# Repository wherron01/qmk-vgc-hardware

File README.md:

# QMK Video Game Controller Hardware
### The OSH HID PC video game controller powered by QMK
KiCAD Files for the PCB.

Implemented using 
- [SparkFun Thumb Joysticks](https://www.sparkfun.com/products/9032)
- [C&K PTS645 Switches](https://www.ckswitches.com/products/switches/product-details/Tactile/PTS645/)
- [Teensy LC](https://www.pjrc.com/teensy/teensyLC.html)

### [OSHPark Project](https://oshpark.com/shared_projects/MazId014)

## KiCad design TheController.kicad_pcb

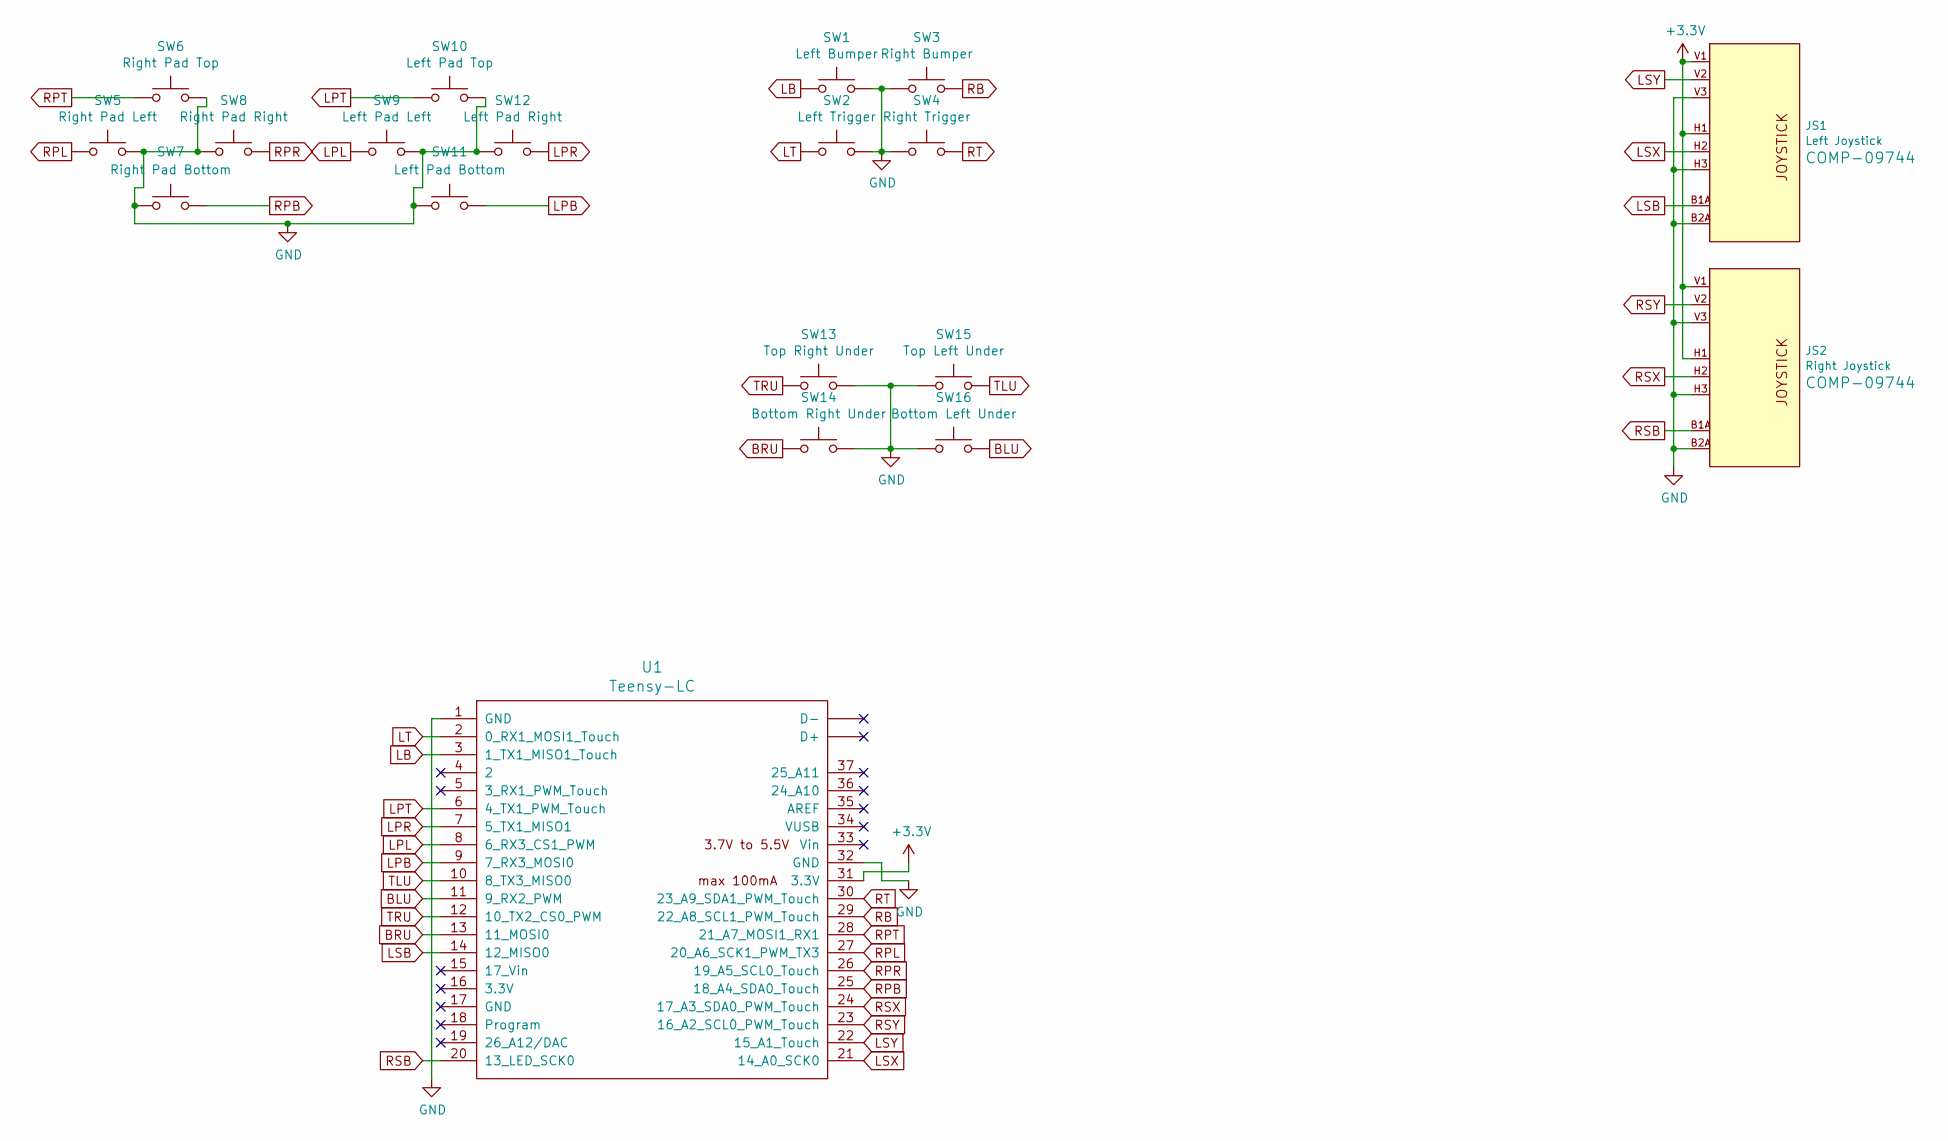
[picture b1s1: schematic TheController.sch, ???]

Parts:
JS1: Left Joystick; JOYSTICK
JS2: Right Joystick; JOYSTICK
SW1: Left Bumper; SW_Tactile_SPST_Angled_PTS645Vx58-2LFS
SW2: Left Trigger; SW_Tactile_SPST_Angled_PTS645Vx58-2LFS
SW3: Right Bumper; SW_Tactile_SPST_Angled_PTS645Vx58-2LFS
SW4: Right Trigger; SW_Tactile_SPST_Angled_PTS645Vx58-2LFS
SW5: Right Pad Left; SW_PUSH_6mm_H8mm
SW6: Right Pad Top; SW_PUSH_6mm_H8mm
SW7: Right Pad Bottom; SW_PUSH_6mm_H8mm
SW8: Right Pad Right; SW_PUSH_6mm_H8mm
SW9: Left Pad Left; SW_PUSH_6mm_H8mm
SW10: Left Pad Top; SW_PUSH_6mm_H8mm
SW11: Left Pad Bottom; SW_PUSH_6mm_H8mm
SW12: Left Pad Right; SW_PUSH_6mm_H8mm
SW13: Top Right Under; SW_PUSH_6mm_H8mm
SW14: Bottom Right Under; SW_PUSH_6mm_H8mm
SW15: Top Left Under; SW_PUSH_6mm_H8mm
SW16: Bottom Left Under; SW_PUSH_6mm_H8mm
U1: Teensy-LC; Teensy30_31_32_LC_ONLY_SIDE

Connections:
+3V3: JS1.H1 (H+), JS1.V1 (V+), JS2.H1 (H+), JS2.V1 (V+), U1.31 (3.3V)
BLU: SW16.1, U1.11 (9_RX2_PWM)
BRU: SW14.1, U1.13 (11_MOSI0)
GND: JS1.B2A (SEL-), JS1.H3 (H-), JS1.MOUN, JS1.V3 (V-), JS2.B2A (SEL-), JS2.H3 (H-), JS2.MOUN, JS2.V3 (V-), SW1.2, SW2.2, SW3.1, SW4.1, SW5.2, SW6.2, SW7.1, SW8.1, SW9.1, SW10.2, SW11.1, SW12.2, SW13.2, SW14.2, SW15.2, SW16.2, U1.1 (GND), U1.32 (GND)
LB: SW1.1, U1.3 (1_TX1_MISO1_Touch)
LPB: SW11.2, U1.9 (7_RX3_MOSI0)
LPL: SW9.2, U1.8 (6_RX3_CS1_PWM)
LPR: SW12.1, U1.7 (5_TX1_MISO1)
LPT: SW10.1, U1.6 (4_TX1_PWM_Touch)
LSB: JS1.B1A (SEL+), U1.14 (12_MISO0)
LSX: JS1.H2 (H), U1.21 (14_A0_SCK0)
LSY: JS1.V2 (V), U1.22 (15_A1_Touch)
LT: SW2.1, U1.2 (0_RX1_MOSI1_Touch)
RB: SW3.2, U1.29 (22_A8_SCL1_PWM_Touch)
RPB: SW7.2, U1.25 (18_A4_SDA0_Touch)
RPL: SW5.1, U1.27 (20_A6_SCK1_PWM_TX3)
RPR: SW8.2, U1.26 (19_A5_SCL0_Touch)
RPT: SW6.1, U1.28 (21_A7_MOSI1_RX1)
RSB: JS2.B1A (SEL+), U1.20 (13_LED_SCK0)
RSX: JS2.H2 (H), U1.24 (17_A3_SDA0_PWM_Touch)
RSY: JS2.V2 (V), U1.23 (16_A2_SCL0_PWM_Touch)
RT: SW4.2, U1.30 (23_A9_SDA1_PWM_Touch)
TLU: SW15.1, U1.10 (8_TX3_MISO0)
TRU: SW13.1, U1.12 (10_TX2_CS0_PWM)

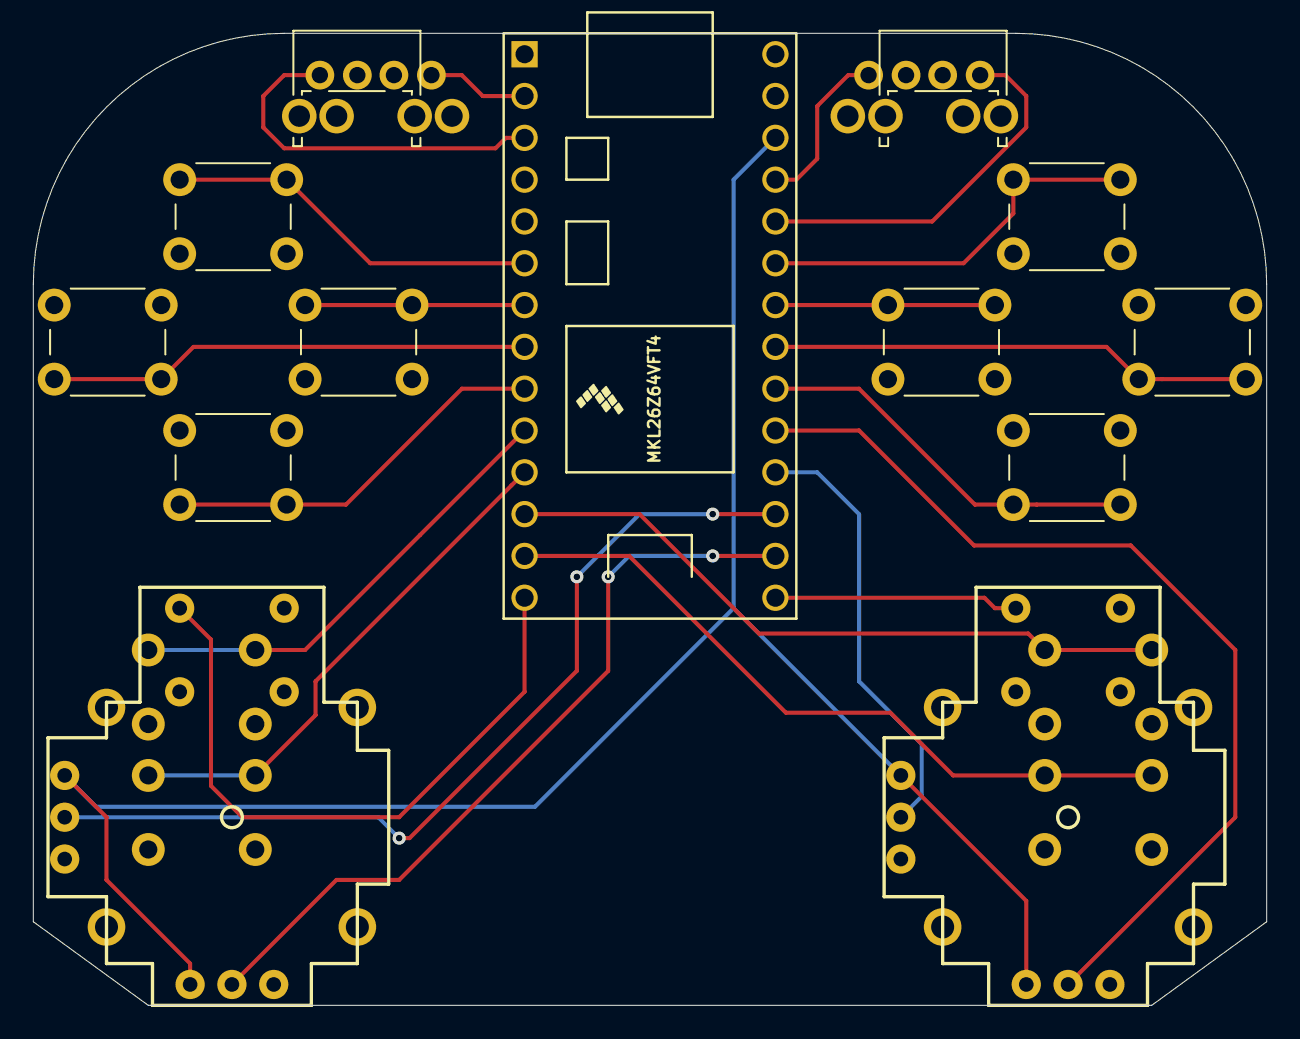
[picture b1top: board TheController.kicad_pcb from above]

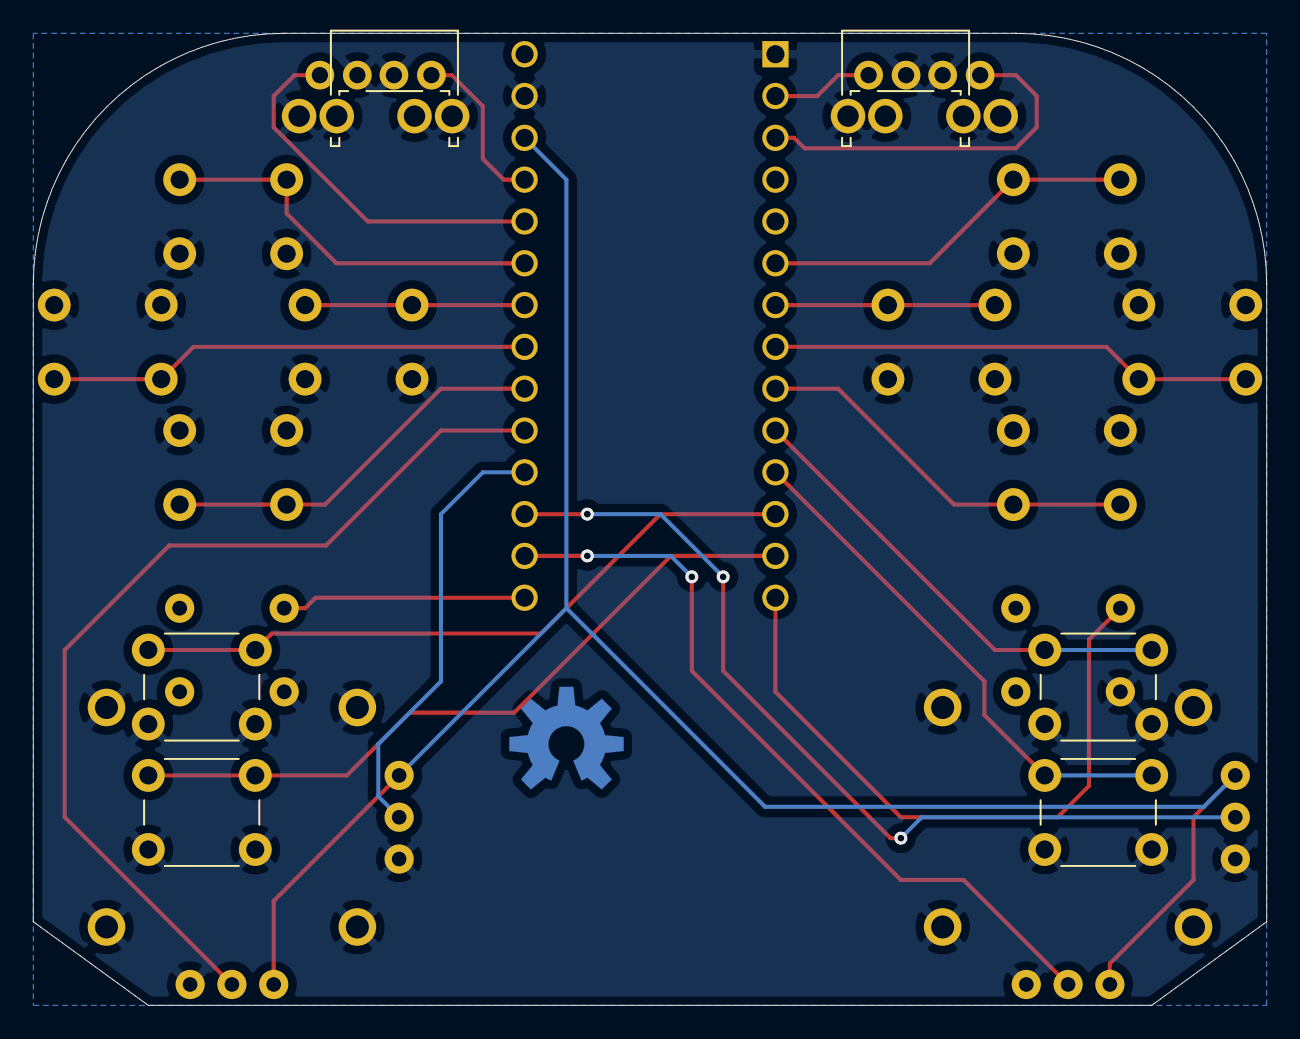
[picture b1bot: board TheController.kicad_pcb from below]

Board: 2 copper layers, 74.9 x 59.1 mm, 19 parts (6 on the bottom side), 24 nets.

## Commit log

2019-09-28 init
